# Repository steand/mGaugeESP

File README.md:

# mGaugeESP

This software is the ESP component of mGauge.

## What is mGauge?

mGauge consists of two components connected via Bluetooth Low Energy (BLE).

## ESP32 Gauge

A measuring device with two functions, based on an ESP32-S3.

The ESP32-S3 was chosen because it supports BLE 5.0, ensuring a secure connection to the mGauge GUI.

- INA219 for measuring DC current
- Voltage: 0-26V
- Current: 0-3.2A
- Power: 0-83.2W
- 3.5" LCD display for current and voltage
- xy-fz35 as an electronic resistor

with a maximum power rating of 35W (1-25V, 0-5A)

### GUI

Qt PC software for displaying and recording measurement data

- Plotting of measured values
- Saving measured values as *.csv files.

Code is available in the  [mGaugeGUI](https://github.com/steand/mGaugeGUI) repository.

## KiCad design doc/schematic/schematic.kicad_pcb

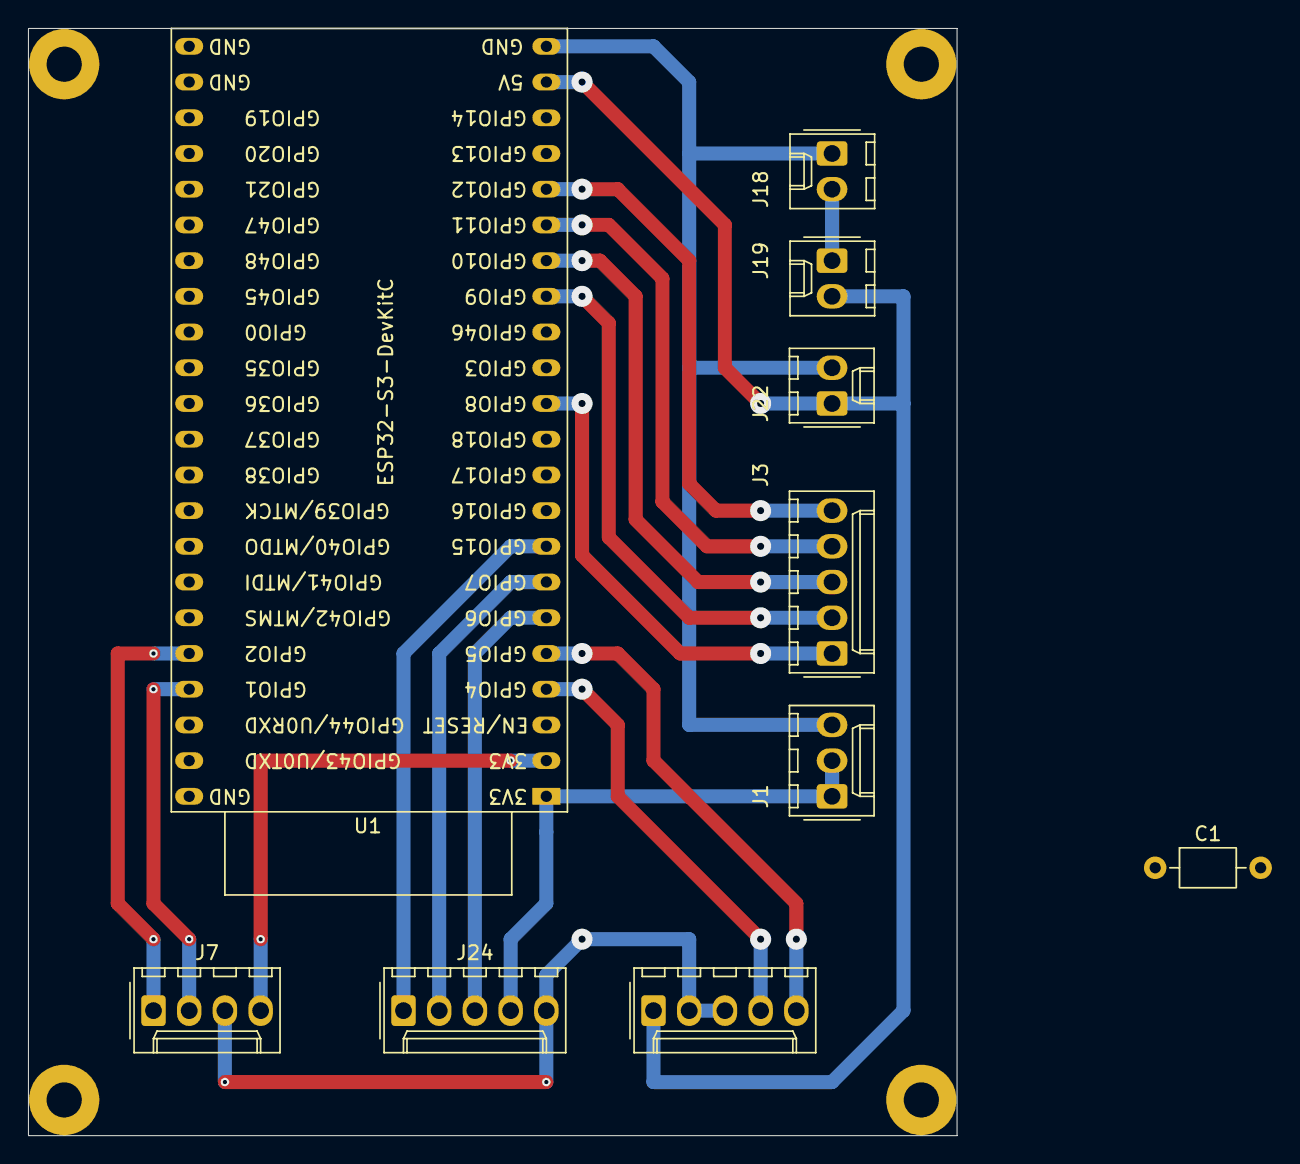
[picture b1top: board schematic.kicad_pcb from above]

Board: 2 copper layers, 66.0 x 78.7 mm, 10 parts (0 on the bottom side), 16 nets.

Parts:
C1: 0,1µ; C_Axial_L3.8mm_D2.6mm_P7.50mm_Horizontal
J1: TFT_Power; Molex_KK-254_AE-6410-03A_1x03_P2.54mm_Vertical
J3: TFT; Molex_KK-254_AE-6410-05A_1x05_P2.54mm_Vertical
J7: INA; Molex_KK-254_AE-6410-04A_1x04_P2.54mm_Vertical
J15: fz35; Molex_KK-254_AE-6410-05A_1x05_P2.54mm_Vertical
J18: USB; Molex_KK-254_AE-6410-02A_1x02_P2.54mm_Vertical
J19: Switch; Molex_KK-254_AE-6410-02A_1x02_P2.54mm_Vertical
J22: Fan; Molex_KK-254_AE-6410-02A_1x02_P2.54mm_Vertical
J24: KY-040; Molex_KK-254_AE-6410-05A_1x05_P2.54mm_Vertical
U1: ESP32-S3-DevKitC

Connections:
+3V3: J1.1, J1.2, J7.4, J24.4, U1.1 (3V3), U1.2 (3V3)
+5V: C1.1, J15.1, J19.2, J22.1, U1.21 (5V)
GND: C1.2, J1.3, J7.3, J15.2, J15.3, J18.1, J22.2, J24.5, U1.22 (GND), U1.44 (GND)
unnamed: J3.1, U1.12 (GPIO8/ADC1_CH7)
unnamed: J3.2, U1.15 (GPIO9/ADC1_CH8)
unnamed: J3.3, U1.16 (GPIO10/ADC1_CH9)
unnamed: J3.4, U1.17 (GPIO11/ADC2_CH0)
unnamed: J3.5, U1.18 (GPIO12/ADC2_CH1)
unnamed: J7.1, U1.40 (GPIO2/ADC1_CH1)
unnamed: J7.2, U1.41 (GPIO1/ADC1_CH0)
unnamed: J15.4, U1.4 (GPIO4/ADC1_CH3)
unnamed: J15.5, U1.5 (GPIO5/ADC1_CH4)
unnamed: J18.2, J19.1
unnamed: J24.1, U1.8 (GPIO15/ADC2_CH4/32K_P)
unnamed: J24.2, U1.7 (GPIO7/ADC1_CH6)
unnamed: J24.3, U1.6 (GPIO6/ADC1_CH5)

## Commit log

2026-02-10 First develop version
2026-02-10 Files moved
2026-02-10 Display complete
2026-02-12 Add schematic
    add schematic build with KiCad
2026-02-12 Update gitignore
2026-02-16 Schema V0.1
2026-02-19 Add 2nd INA219 & modify display.
    ToDo: implementation of FZ35
2026-02-21 full functionality
2026-02-21 comment TESTDATA_ON
2026-02-24 code optimization
    1.) centralization of data in a global class
    2.) make Display as a global class
    3.) code optimization
    4.) prepare for a setup dialog
    this version not able for production
2026-02-24 Stable for testing
    all functions avalible:
    1. INA219 complete
    1.1 KY-040 and dialog for setup INA219 Resistor
    2. Fz35 ready to send data to bluetooth
    3. Bluetooth already but not tested
    doc:
2026-02-24 update schematic
2026-03-22 Bug Fix for V1.0.0-pre_alpha
